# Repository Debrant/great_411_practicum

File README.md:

great_411_practicum
===================

Fall 2014 Industry Design Practicum at PSU

#[Project Wiki](https://github.com/Debrant/great_411_practicum/wiki)

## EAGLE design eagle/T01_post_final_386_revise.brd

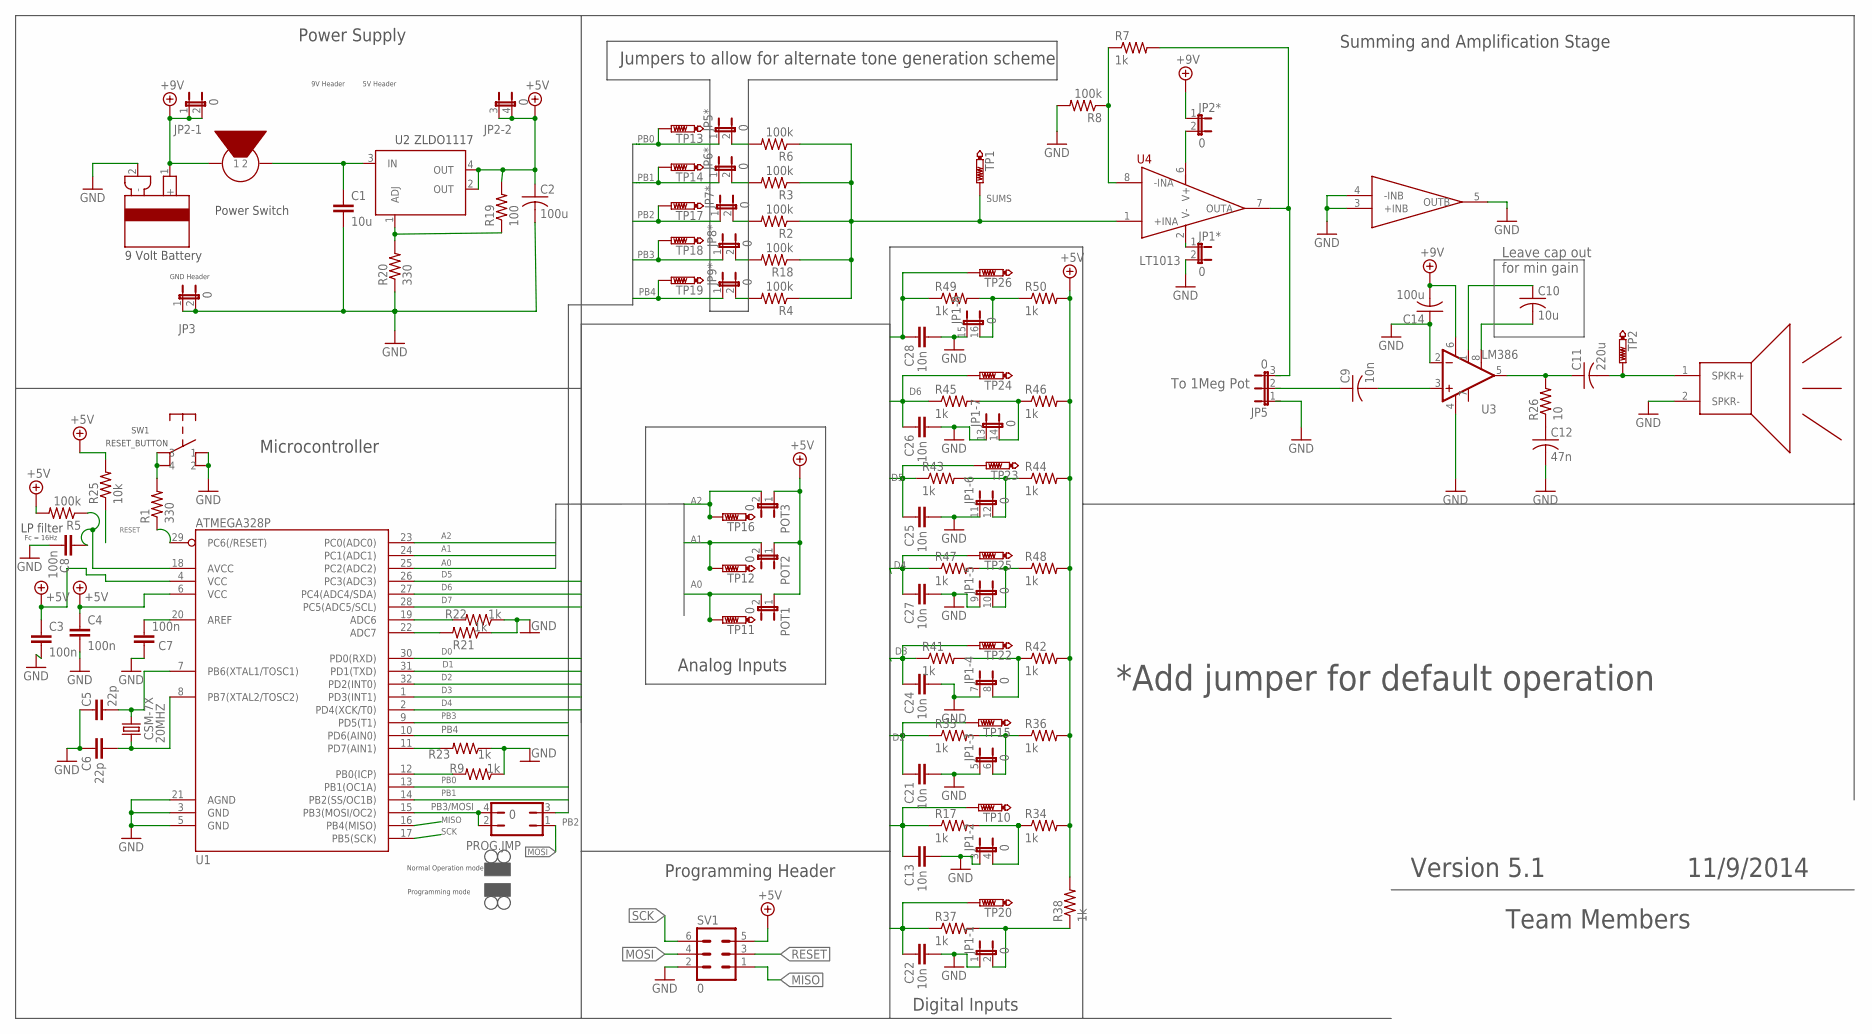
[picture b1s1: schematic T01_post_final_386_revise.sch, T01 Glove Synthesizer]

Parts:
20MHZ: CSM-7X; CSM-7X-DU
C1: 10u; 0603-CAP
C2: 100u; C075-042X103
C3, C4, C7, C8: 100n; 0603-CAP
C5, C6: 22p; 0603-CAP
C9: 10n; C025-030X050
C10: 10u; C025-030X050
C11: 220u; C025-030X050
C12: 47n; C025-030X050
C13, C21, C22, C24, C25, C26, C27, C28: 10n; 0603-CAP
C14: 100u; C025-030X050
JP1: 0; JP8Q
JP1*, JP2*, JP3, JP5*, JP6*, JP7*, JP8*, JP9*: 0; JP1
JP2: 0; JP2Q
JP5: 0; JP2
POT1, POT2, POT3: 0; JP1
PROG.JMP: 0; JP2Q
R1, R20: 330; 0603-RES
R2, R3, R4, R5, R6, R8, R18: 100k; 0603-RES
R7, R9, R17, R21, R22, R23, R34, R35, R36, R37, R38, R41, R42, R43, R44, R45, R46, R47, R48, R49, R50: 1k; 0603-RES
R19: 100; 0603-RES
R25: 10k; 0603-RES
R26: 10; 0204V
SV1: 0; MA03-2
SW1: RESET_BUTTON
TP1, TP2, TP10, TP11, TP12, TP13, TP14, TP15, TP16, TP17, TP18, TP19, TP20, TP22, TP23, TP24, TP25, TP26: PTR1B2,54; B2,54
U1: ATMEGA328P; TQFP32-08
U2: ZLDO1117; SOT223
U3: LM386; DIP08
U4: LT1013; SO08
U$1: SPEAKER; JP1
U$7: POWER_SWITCH; JP1
U$8: 9VOLTBATTERY; JP1

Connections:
+5V: C2.1, C3.1, C4.1, JP2.3 (1), JP2.4 (2), POT1.1, POT2.1, POT3.1, R5.2, R19.2, R25.2, R34.2, R36.2, R38.2, R42.2, R44.2, R46.2, R48.2, R50.2, SV1.5, U1.4 (VCC), U1.6 (VCC), U2.2 (OUT), U2.4 (OUT)
+9V: C14.2, JP2.1, JP2.2, JP2*.1, U3.6 (V+), U$7.1, U$8.1 (+)
A0: POT1.2, TP11.TP, U1.25 (PC2(ADC2))
A1: POT2.2, TP12.TP, U1.24 (PC1(ADC1))
A2: POT3.2, TP16.TP, U1.23 (PC0(ADC0))
D0: C22.2, R37.1, TP20.TP, U1.30 (PD0(RXD))
D1: C13.2, R17.1, TP10.TP, U1.31 (PD1(TXD))
D2: C21.2, R35.1, TP15.TP, U1.32 (PD2(INT0))
D3: C24.2, R41.1, TP22.TP, U1.1 (PD3(INT1))
D4: C27.2, R47.1, TP25.TP, U1.2 (PD4(XCK/T0))
D5: C25.2, R43.1, TP23.TP, U1.26 (PC3(ADC3))
D6: C26.2, R45.1, TP24.TP, U1.27 (PC4(ADC4/SDA))
D7: C28.2, R49.1, TP26.TP, U1.28 (PC5(ADC5/SCL))
GND: C1.2, C2.2, C3.2, C4.2, C5.2, C6.2, C7.2, C8.2, C12.2, C13.1, C14.1, C21.1, C22.1, C24.1, C25.1, C26.1, C27.1, C28.1, JP1.1, JP1.3 (1), JP1.5 (1), JP1.7 (1), JP1.9 (1), JP1.11 (1), JP1.13 (1), JP1.15 (1), JP1*.2, JP3.1, JP3.2, R8.2, R9.1, R20.1, R21.1, R22.1, R23.1, SV1.2, SW1.1, SW1.2, U1.3 (GND), U1.5 (GND), U1.21 (AGND), U3.2 (-IN), U3.4 (V-), U4.3 (+INB), U4.4 (-INB), U4.5 (OUTB), U$1.2 (SPKR-), U$8.2 (-)
MISO: SV1.1, U1.16 (PB4(MISO))
MOSI: PROG.JMP.1, SV1.4
unnamed: C7.1, U1.20 (AREF)
unnamed: JP1.8 (2), R41.2, R42.1
unnamed: JP1.12 (2), R43.2, R44.1
unnamed: R1.1, U1.29 (PC6(/RESET))
unnamed: R7.2, U4.7 (OUTA)
unnamed: 20MHZ.1, C5.1, U1.7 (PB6(XTAL1/TOSC1))
unnamed: 20MHZ.2, C6.1, U1.8 (PB7(XTAL2/TOSC2))
unnamed: C8.1, R5.1, U1.18 (AVCC)
unnamed: R21.2, U1.22 (ADC7)
unnamed: R22.2, U1.19 (ADC6)
unnamed: C9.2, U3.3 (+IN)
unnamed: JP1.6 (2), R35.2, R36.1
unnamed: R7.1, R8.1, U4.8 (-INA)
unnamed: R9.2, U1.12 (PB0(ICP))
unnamed: JP5*.2, R6.2
unnamed: JP9*.2, R4.2
unnamed: R1.2, SW1.3, SW1.4
unnamed: JP1.4 (2), R17.2, R34.1
unnamed: JP8*.2, R18.2
unnamed: C10.1, U3.1 (GAIN)
unnamed: C11.2, TP2.TP, U$1.1 (SPKR+)
unnamed: JP7*.2, R2.2
unnamed: JP2*.2, U4.6 (V+)
unnamed: R19.1, R20.2, U2.1 (ADJ)
unnamed: C1.1, U2.3 (IN), U$7.2
unnamed: JP6*.2, R3.2
unnamed: C10.2, U3.8 (GAIN)
unnamed: JP1.2, R37.2, R38.1
unnamed: C11.1, R26.2, U3.5 (OUT)
unnamed: C12.1, R26.1
unnamed: JP1.14 (2), R45.2, R46.1
unnamed: JP1.10 (2), R47.2, R48.1
unnamed: JP1.16 (2), R49.2, R50.1
PB0: JP5*.1, TP13.TP, U1.13 (PB1(OC1A))
PB1: JP6*.1, TP14.TP, U1.14 (PB2(SS/OC1B))
PB2: JP7*.1, PROG.JMP.3, TP17.TP
PB3: JP8*.1, TP18.TP, U1.9 (PD5(T1))
PB3/MOSI: PROG.JMP.2, PROG.JMP.4, U1.15 (PB3(MOSI/OC2))
PB4: JP9*.1, TP19.TP, U1.10 (PD6(AIN0))
PD7: R23.2, U1.11 (PD7(AIN1))
RESET: R25.1, SV1.3
SCK: SV1.6, U1.17 (PB5(SCK))
SUMS: R2.1, R3.1, R4.1, R6.1, R18.1, TP1.TP, U4.1 (+INA)
V-: JP1*.1, U4.2 (V-)

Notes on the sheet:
Power Switch
Programming Header
Digital Inputs
Power Supply
Microcontroller
Summing and Amplification Stage
Analog Inputs
LP filter
*Add jumper for default operation
5V Header
9V Header
GND Header
Fc = 16Hz
Jumpers to allow for alternate tone generation scheme
Programming mode
Normal Operation mode
Team Members
Version 5.1
11/9/2014
To 1Meg Pot
Leave cap out for min gain

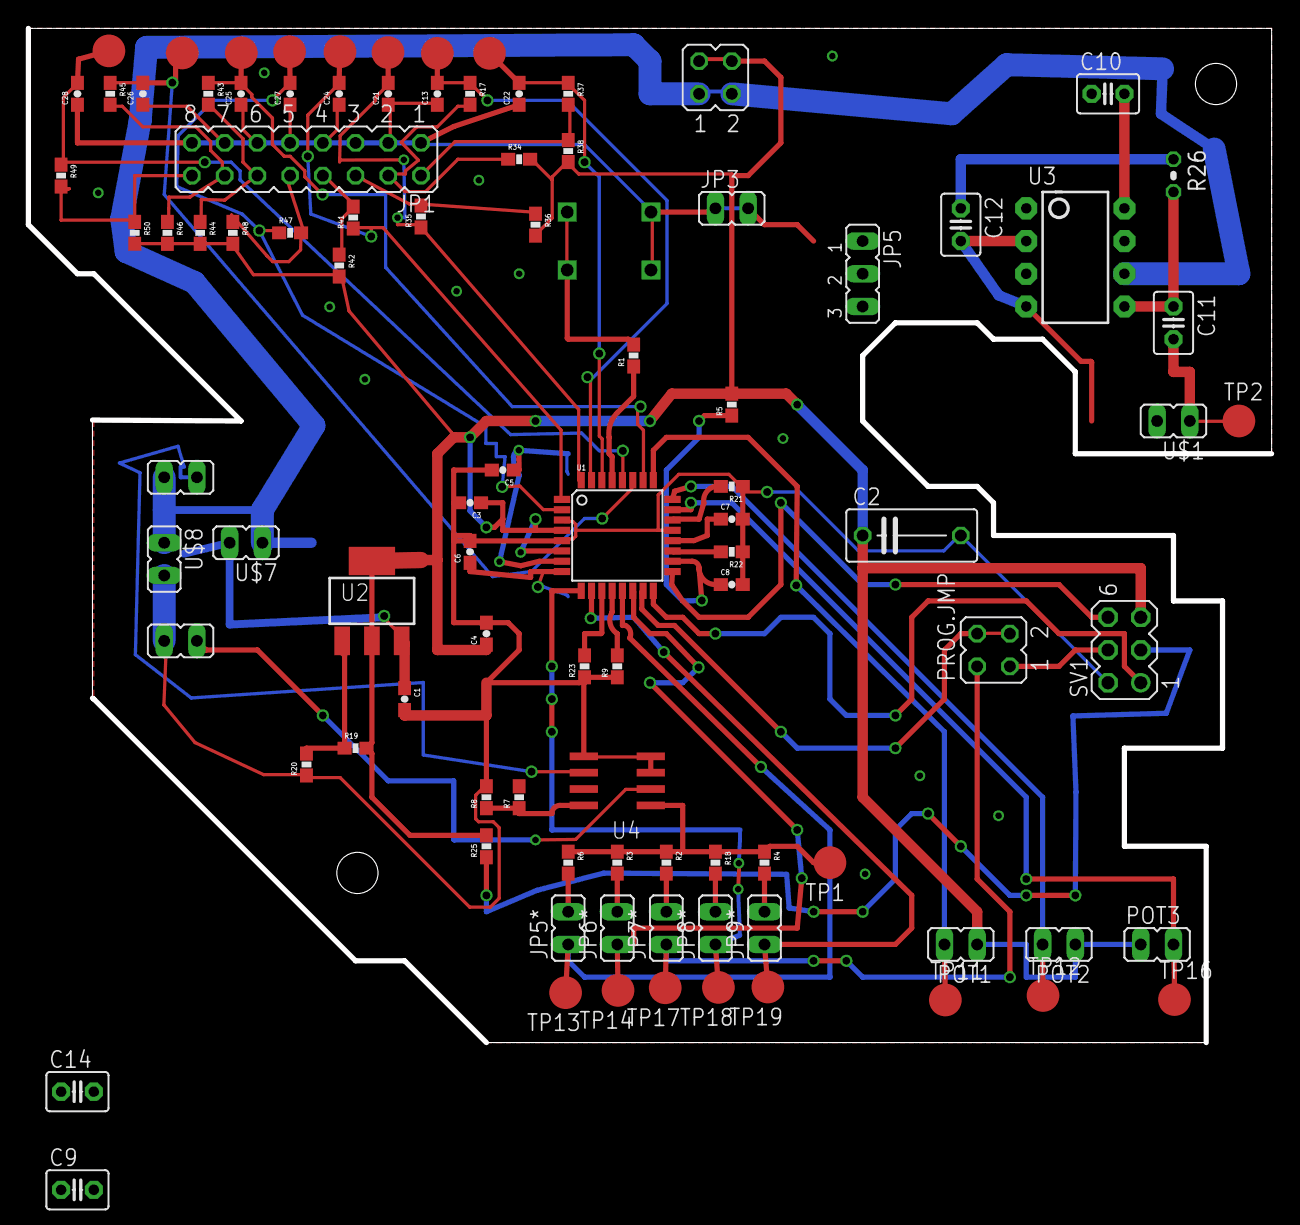
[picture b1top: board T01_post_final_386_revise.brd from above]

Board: 2 copper layers, 96.5 x 78.7 mm, 97 parts (1 on the bottom side), 60 nets.

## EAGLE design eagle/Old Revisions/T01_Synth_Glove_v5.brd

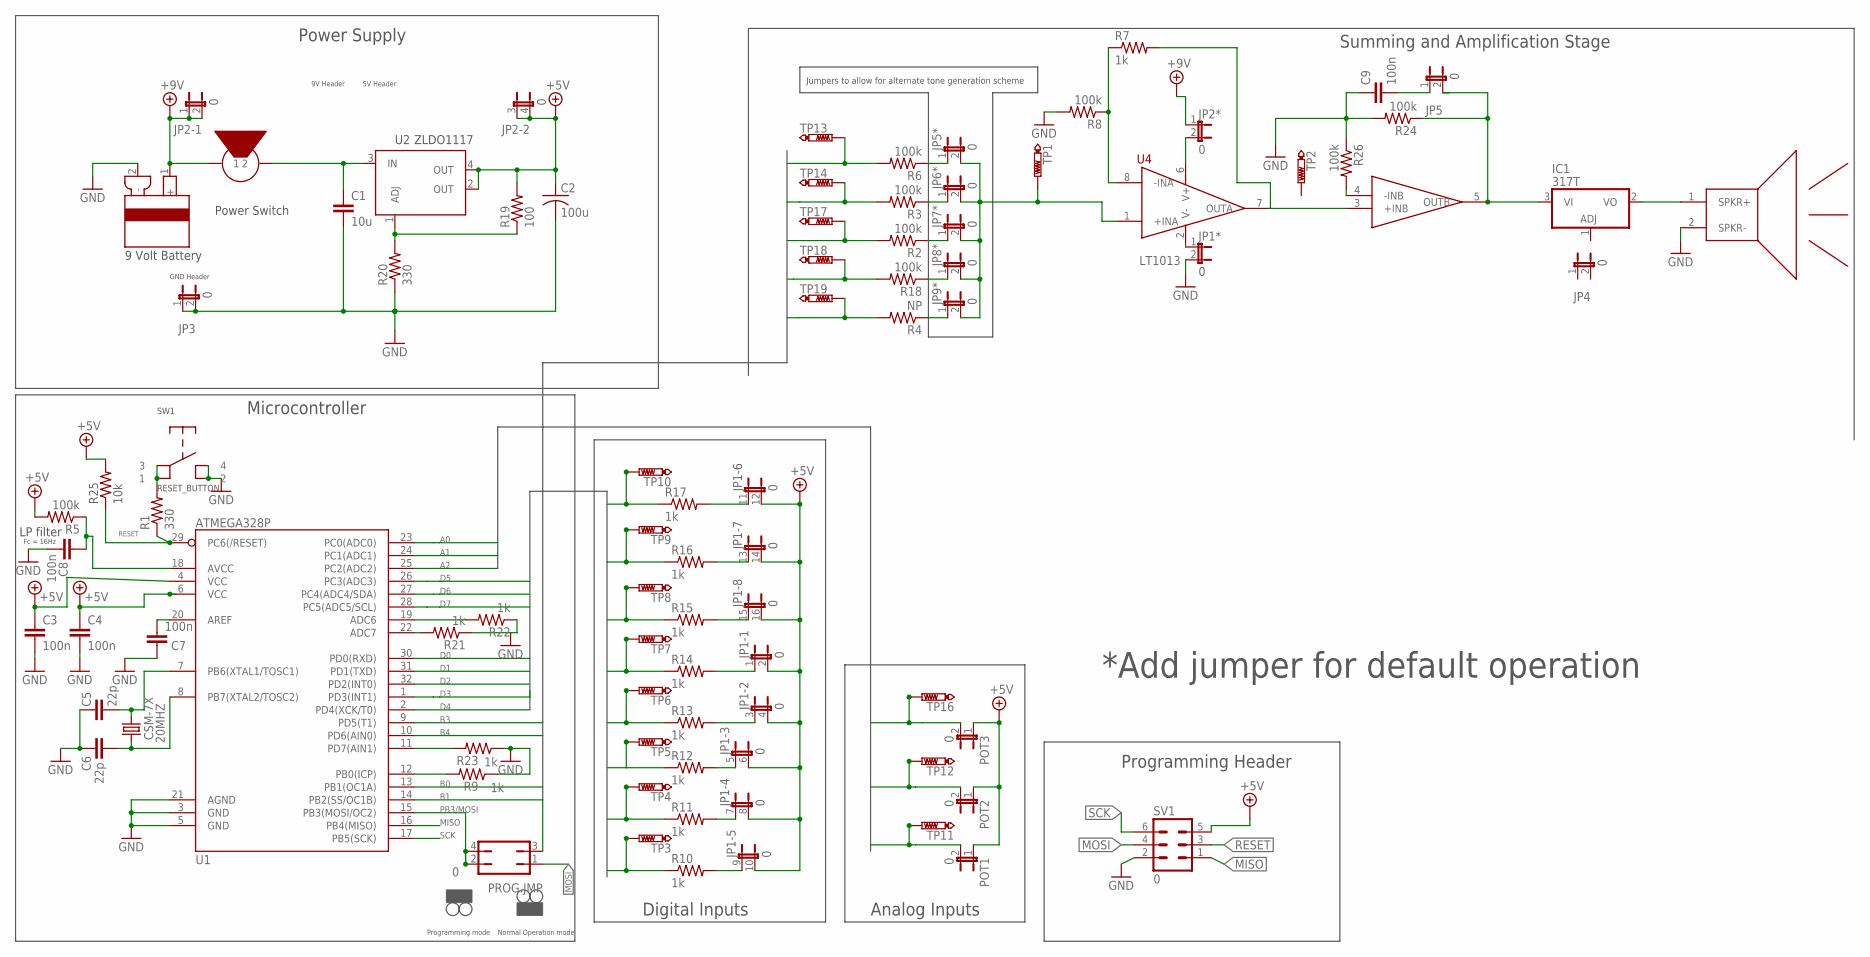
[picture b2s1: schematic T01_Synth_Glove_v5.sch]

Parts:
20MHZ: CSM-7X; CSM-7X-DU
C1: 10u; 0603-CAP
C2: 100u; C075-042X103
C3, C4, C7, C8, C9: 100n; 0603-CAP
C5, C6: 22p; 0603-CAP
IC1: 317T; TO220H
JP1: 0; JP8Q
JP1*, JP2*, JP3, JP4, JP5, JP5*, JP6*, JP7*, JP8*, JP9*: 0; JP1
JP2: 0; JP2Q
POT1, POT2, POT3: 0; JP1
PROG.JMP: 0; JP2Q
R1, R20: 330; 0603-RES
R2, R3, R5, R6, R8, R18, R24, R26: 100k; 0603-RES
R4: NP; 0603-RES
R7, R9, R10, R11, R12, R13, R14, R15, R16, R17, R21, R22, R23: 1k; 0603-RES
R19: 100; 0603-RES
R25: 10k; 0603-RES
SV1: 0; MA03-2
SW1: RESET_BUTTON
TP1, TP2, TP3, TP4, TP5, TP6, TP7, TP8, TP9, TP10, TP11, TP12, TP13, TP14, TP16, TP17, TP18, TP19: PTR1B2,54; B2,54
U1: ATMEGA328P; TQFP32-08
U2: ZLDO1117; SOT223
U4: LT1013; SO08
U$1: SPEAKER; JP1
U$7: POWER_SWITCH; JP1
U$8: 9VOLTBATTERY; JP1

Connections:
+5V: C2.1, C3.1, C4.1, JP1.2, JP1.4 (2), JP1.6 (2), JP1.8 (2), JP1.10 (2), JP1.12 (2), JP1.14 (2), JP1.16 (2), JP2.3 (1), JP2.4 (2), POT1.1, POT2.1, POT3.1, R5.2, R19.2, R25.2, SV1.5, U1.4 (VCC), U1.6 (VCC), U2.2 (OUT), U2.4 (OUT)
+9V: JP2.1, JP2.2, JP2*.1, U$7.1, U$8.1 (+)
A0: POT1.2, TP11.TP, U1.23 (PC0(ADC0))
A1: POT2.2, TP12.TP, U1.24 (PC1(ADC1))
A2: POT3.2, TP16.TP, U1.25 (PC2(ADC2))
B0: R6.2, TP13.TP, U1.13 (PB1(OC1A))
B1: R2.2, R3.2, TP14.TP, TP17.TP, U1.14 (PB2(SS/OC1B))
B2: PROG.JMP.3
B3: R18.2, TP18.TP, U1.9 (PD5(T1))
B4: R4.2, TP19.TP, U1.10 (PD6(AIN0))
D0: R10.1, TP3.TP, U1.30 (PD0(RXD))
D1: R11.1, TP4.TP, U1.31 (PD1(TXD))
D2: R12.1, TP5.TP, U1.32 (PD2(INT0))
D3: R13.1, TP6.TP, U1.1 (PD3(INT1))
D4: R14.1, TP7.TP, U1.2 (PD4(XCK/T0))
D5: R15.1, TP8.TP, U1.26 (PC3(ADC3))
D6: R16.1, TP9.TP, U1.27 (PC4(ADC4/SDA))
D7: R17.1, TP10.TP, U1.28 (PC5(ADC5/SCL))
GND: C1.2, C2.2, C3.2, C4.2, C5.2, C6.2, C7.2, C8.2, C9.1, JP1*.2, JP3.1, JP3.2, R8.2, R9.1, R20.1, R21.1, R22.1, R23.1, R24.2, R26.1, SV1.2, SW1.2, SW1.4, U1.3 (GND), U1.5 (GND), U1.21 (AGND), U$1.2 (SPKR-), U$8.2 (-)
MISO: SV1.1, U1.16 (PB4(MISO))
MOSI: PROG.JMP.1, SV1.4
unnamed: C7.1, U1.20 (AREF)
unnamed: JP5*.2, JP6*.2, JP7*.2, JP8*.2, JP9*.2, TP1.TP, U4.1 (+INA)
unnamed: JP1.9 (1), R10.2
unnamed: JP1.7 (1), R11.2
unnamed: JP1.5 (1), R12.2
unnamed: 20MHZ.1, C5.1, U1.7 (PB6(XTAL1/TOSC1))
unnamed: 20MHZ.2, C6.1, U1.8 (PB7(XTAL2/TOSC2))
unnamed: C8.1, R5.1, U1.18 (AVCC)
unnamed: R21.2, U1.22 (ADC7)
unnamed: R22.2, U1.19 (ADC6)
unnamed: JP1.3 (1), R13.2
unnamed: JP1.1, R14.2
unnamed: JP1.15 (1), R15.2
unnamed: JP1.13 (1), R16.2
unnamed: R7.1, R8.1, U4.8 (-INA)
unnamed: R9.2, U1.12 (PB0(ICP))
unnamed: JP5*.1, R6.1
unnamed: JP6*.1, R3.1
unnamed: R1.2, SW1.1, SW1.3
unnamed: JP1.11 (1), R17.2
unnamed: JP7*.1, R2.1
unnamed: R26.2, U4.4 (-INB)
unnamed: JP8*.1, R18.1
unnamed: IC1.2 (VO), U$1.1 (SPKR+)
unnamed: JP9*.1, R4.1
unnamed: JP2*.2, U4.6 (V+)
unnamed: R7.2, U4.7 (OUTA)
unnamed: R19.1, R20.2, U2.1 (ADJ)
unnamed: C1.1, U2.3 (IN), U$7.2
unnamed: C9.2, JP5.1
unnamed: IC1.3 (VI), JP5.2, R24.1, U4.5 (OUTB)
PB3/MOSI: PROG.JMP.2, PROG.JMP.4, U1.15 (PB3(MOSI/OC2))
PD7: R23.2, U1.11 (PD7(AIN1))
RESET: R1.1, R25.1, SV1.3, U1.29 (PC6(/RESET))
SCK: SV1.6, U1.17 (PB5(SCK))
V-: JP1*.1, U4.2 (V-)

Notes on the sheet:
Power Switch
Programming Header
Digital Inputs
Power Supply
Microcontroller
Summing and Amplification Stage
Analog Inputs
LP filter
*Add jumper for default operation
5V Header
9V Header
GND Header
Fc = 16Hz
Jumpers to allow for alternate tone generation scheme
Programming mode
Normal Operation mode

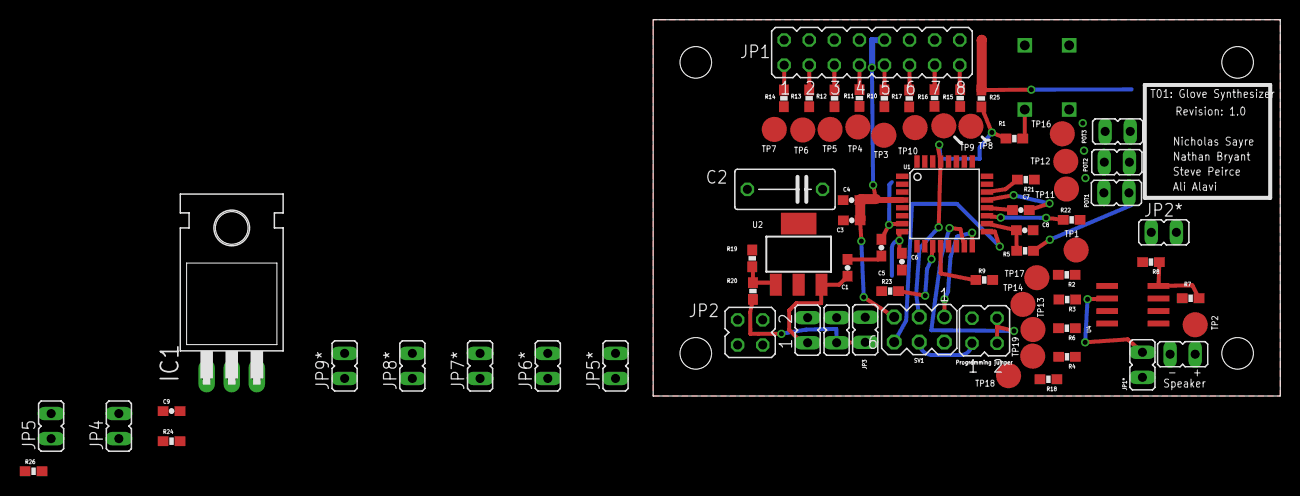
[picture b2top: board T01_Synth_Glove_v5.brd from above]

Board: 2 copper layers, 63.5 x 38.1 mm, 79 parts (1 on the bottom side), 56 nets.

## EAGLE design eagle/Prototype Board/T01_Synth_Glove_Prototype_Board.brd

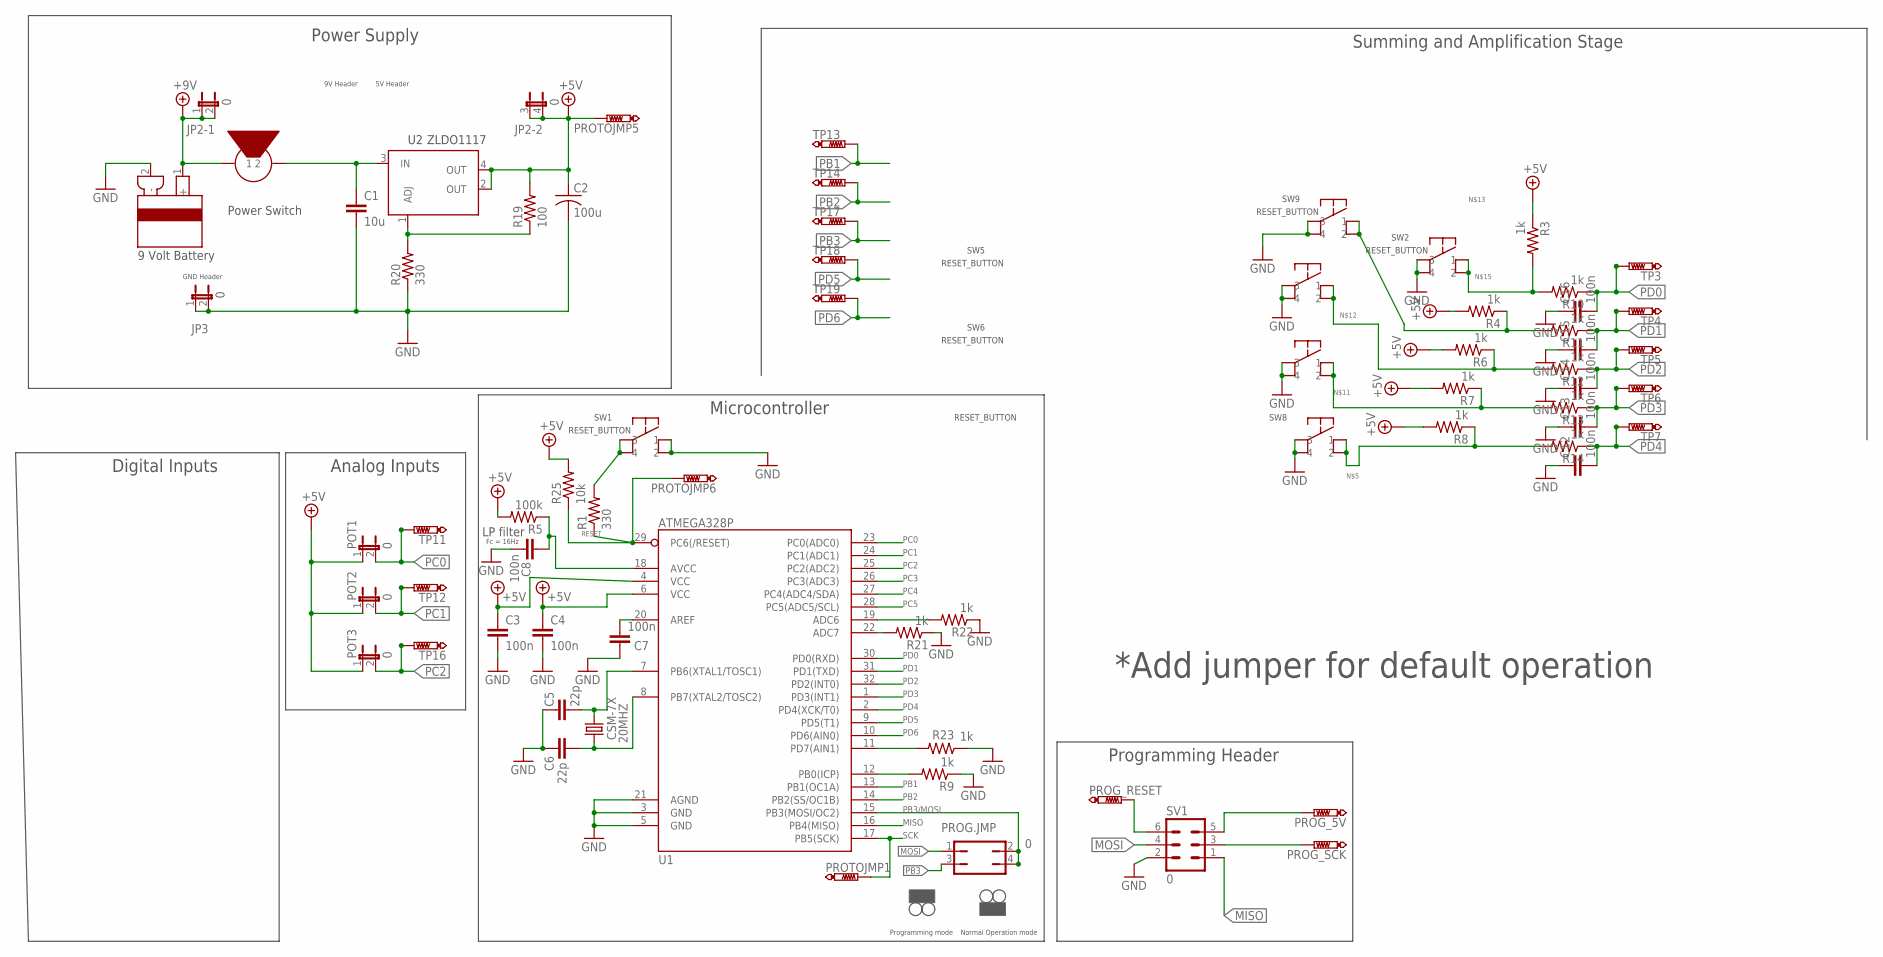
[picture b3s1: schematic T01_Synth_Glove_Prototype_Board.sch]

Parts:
20MHZ: CSM-7X; CSM-7X-DU
C1: 10u; 0603-CAP
C2: 100u; C075-042X103
C3, C4, C7, C8, C12, C13, C14, C15, C16: 100n; 0603-CAP
C5, C6: 22p; 0603-CAP
JP2: 0; JP2Q
JP3: 0; JP1
POT1, POT2, POT3: 0; JP1
PROG.JMP: 0; JP2Q
PROG_5V: PTR1B2,54; B2,54
PROG_RESET: PTR1B2,54; B2,54
PROG_SCK: PTR1B2,54; B2,54
PROTOJMP1, PROTOJMP5, PROTOJMP6: PTR1B2,54; B2,54
R1, R20: 330; 0603-RES
R3, R4, R6, R7, R8, R9, R10, R11, R12, R13, R14, R21, R22, R23: 1k; 0603-RES
R5: 100k; 0603-RES
R19: 100; 0603-RES
R25: 10k; 0603-RES
SV1: 0; MA03-2
SW1, SW2, SW5, SW6, SW8, SW9: RESET_BUTTON
TP3, TP4, TP5, TP6, TP7, TP11, TP12, TP13, TP14, TP16, TP17, TP18, TP19: PTR1B2,54; B2,54
U1: ATMEGA328P; TQFP32-08
U2: ZLDO1117; SOT223
U$7: POWER_SWITCH; JP1
U$8: 9VOLTBATTERY; JP1

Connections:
+5V: C2.1, C3.1, C4.1, JP2.3 (1), JP2.4 (2), POT1.1, POT2.1, POT3.1, PROTOJMP5.TP, R3.1, R4.2, R5.2, R6.2, R7.2, R8.2, R19.2, R25.2, U1.4 (VCC), U1.6 (VCC), U2.2 (OUT), U2.4 (OUT)
+9V: JP2.1, JP2.2, U$7.1, U$8.1 (+)
GND: C1.2, C2.2, C3.2, C4.2, C5.2, C6.2, C7.2, C8.2, C12.1, C13.1, C14.1, C15.1, C16.1, JP3.1, JP3.2, R9.1, R20.1, R21.1, R22.1, R23.1, SV1.2, SW1.1, SW1.2, SW2.3, SW2.4, SW5.3, SW5.4, SW6.3, SW6.4, SW8.3, SW8.4, SW9.3, SW9.4, U1.3 (GND), U1.5 (GND), U1.21 (AGND), U$8.2 (-)
JP3: PROG_SCK.TP, SV1.3
MISO: SV1.1, U1.16 (PB4(MISO))
MOSI: PROG.JMP.1, SV1.4
unnamed: C7.1, U1.20 (AREF)
unnamed: PROG_5V.TP, SV1.5
unnamed: R8.1, R14.2, SW8.1, SW8.2
unnamed: 20MHZ.1, C5.1, U1.7 (PB6(XTAL1/TOSC1))
unnamed: 20MHZ.2, C6.1, U1.8 (PB7(XTAL2/TOSC2))
unnamed: C8.1, R5.1, U1.18 (AVCC)
unnamed: R21.2, U1.22 (ADC7)
unnamed: R22.2, U1.19 (ADC6)
unnamed: R7.1, R13.2, SW6.1, SW6.2
unnamed: R6.1, R12.2, SW5.1, SW5.2
unnamed: R4.1, R11.2, SW9.1, SW9.2
unnamed: R3.2, R10.2, SW2.1, SW2.2
unnamed: R9.2, U1.12 (PB0(ICP))
unnamed: R1.2, SW1.3, SW1.4
unnamed: R19.1, R20.2, U2.1 (ADJ)
unnamed: C1.1, U2.3 (IN), U$7.2
PB1: TP13.TP, U1.13 (PB1(OC1A))
PB2: TP14.TP, U1.14 (PB2(SS/OC1B))
PB3: PROG.JMP.3, TP17.TP
PB3/MOSI: PROG.JMP.2, PROG.JMP.4, U1.15 (PB3(MOSI/OC2))
PC0: POT1.2, TP11.TP, U1.23 (PC0(ADC0))
PC1: POT2.2, TP12.TP, U1.24 (PC1(ADC1))
PC2: POT3.2, TP16.TP, U1.25 (PC2(ADC2))
PC3: U1.26 (PC3(ADC3))
PC4: U1.27 (PC4(ADC4/SDA))
PC5: U1.28 (PC5(ADC5/SCL))
PD0: C16.2, R10.1, TP3.TP, U1.30 (PD0(RXD))
PD1: C15.2, R11.1, TP4.TP, U1.31 (PD1(TXD))
PD2: C14.2, R12.1, TP5.TP, U1.32 (PD2(INT0))
PD3: C13.2, R13.1, TP6.TP, U1.1 (PD3(INT1))
PD4: C12.2, R14.1, TP7.TP, U1.2 (PD4(XCK/T0))
PD5: TP18.TP, U1.9 (PD5(T1))
PD6: TP19.TP, U1.10 (PD6(AIN0))
PD7: R23.2, U1.11 (PD7(AIN1))
PJ4: PROG_RESET.TP, SV1.6
RESET: PROTOJMP6.TP, R1.1, R25.1, U1.29 (PC6(/RESET))
SCK: PROTOJMP1.TP, U1.17 (PB5(SCK))

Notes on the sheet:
Power Switch
Programming Header
Digital Inputs
Power Supply
Microcontroller
Summing and Amplification Stage
Analog Inputs
LP filter
*Add jumper for default operation
5V Header
9V Header
GND Header
Fc = 16Hz
Programming mode
Normal Operation mode

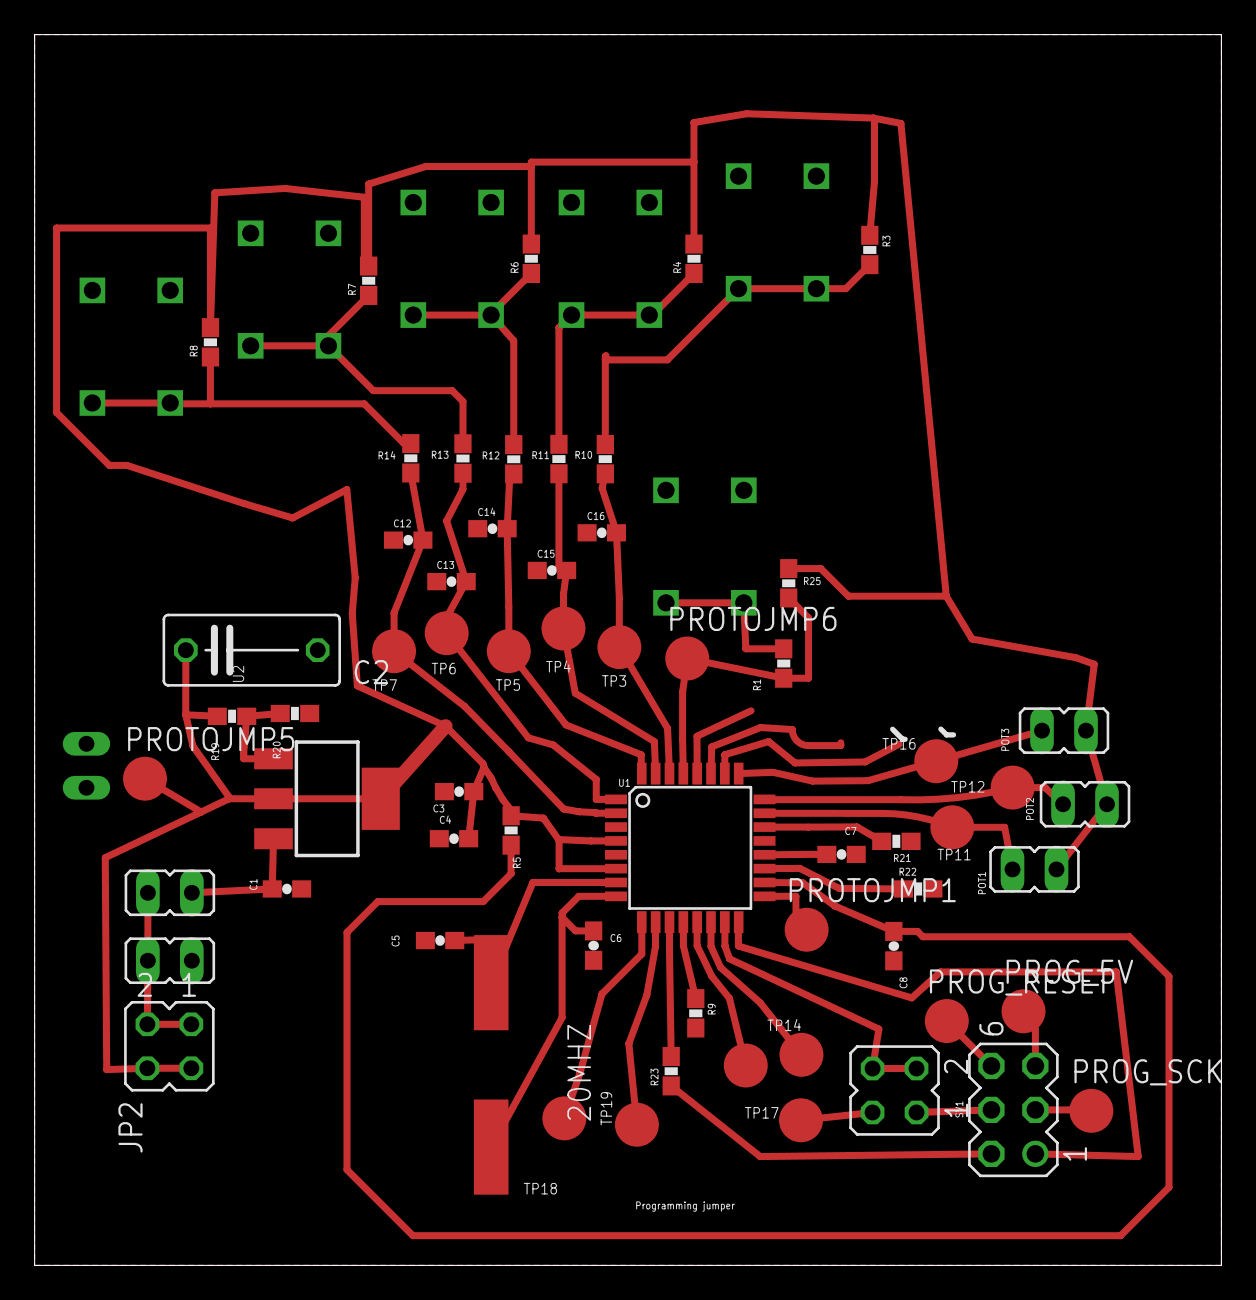
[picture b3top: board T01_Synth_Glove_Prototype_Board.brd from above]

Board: 2 copper layers, 68.6 x 71.1 mm, 69 parts (1 on the bottom side), 40 nets.

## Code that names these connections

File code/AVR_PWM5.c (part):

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
	/*PRTIMx BIT MUST BE WRITTEN 0 TO ENABLE TIMER/COUNTERS P.94 DS*/
	/*OUTPUT COMPARE REGISTERS, OUR (5) PWM OUTPUTS:*/
	OCR0A = TONE0.PULSE_WIDTH;//PIN 10, PD6
	OCR0B = TONE1.PULSE_WIDTH;//PIN 9,  PD5
	OCR1AL = TONE2.PULSE_WIDTH;//PIN 13, PB1
	OCR1BL = TONE3.PULSE_WIDTH;//PIN 14, PB2
	OCR2A = TONE4.PULSE_WIDTH;//PIN 15, PB3

	/*TIMER INTERRUPT FLAG REGISTERS:*/
	/*P.110***********COMPARE0B**COMPARE0A*TIMER OVERFLOW*******************/
	/*BITS:[7:3]RES, [2]OCF0B, [1]OCF0A, [0]TOV0*/
	/*MAY NEED AN ISR THAT IS A CATCH-ALL, DIRECTS BASED ON FLAGS...*/
	/*SET WHEN OVERFLOW OCCURS, CLEARED BY INTERRUPT TIFRnx:*/
	//TIFR0 |= ();//8-BIT->PORTS:  [OC0A,PD6], [OC0B,PD5]
	//TIFR1 |= ();//16-BIT->PORTS: [OC1A,PB1], [OC1B,PB2]
	//TIFR2 |= ();//8-BIT->PORTS:  [OC2A,PB3], [OC2B,PD3]

	//TIMSK0 |= ((1<<OCIE0A) | (1<<OCIE0B));
	//TIMSK1 |= ((1<<OCIE1A) | (1<<OCIE1B));
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}/*end init*/

void adc_init(){
	//ADMUX |= ((1<<MUX0) | (1<<REFS0)); //ADC1 ON PIN PC1, PIN 24, (TQFP AND DIP)
	ADMUX = 0b01100011; //ADC1 ON PIN PC1, PIN 24, (TQFP AND DIP), P.254
	ADCSRA |= ((1<<ADEN) | (1<<ADIE) | (1<<ADATE | (1<<ADPS0)));//P255,256
	//ADCSRB |= ((1<<ADTS2) | (1<<ADTS1));
	ADCSRB = 0x00; //FREE RUNNING MODE
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
void pwm_update(uint8_t ADC_IN){
		/*TODO: TRY SETTING ONE OCRx SETTING TO '0', SPOOF MULTI IO*/
	if(!INPUT.SW3){//PD0
		OCR1AL = TONE0.PULSE_WIDTH;
		//OCR1AL = (ADC_IN/TONE0.PULSE_WIDTH);
		//OCR1AL = TONE0.PULSE_WIDTH;
		OCR1BL = (ADC_IN/(TONE0.PULSE_WIDTH/16));
	}		
	if(!INPUT.SW4){//PD1
		OCR1AL = TONE1.PULSE_WIDTH*4;
		OCR1BL = TONE3.PULSE_WIDTH*32;
	}
	if(!INPUT.SW5){//PD2
		OCR1AL = TONE2.PULSE_WIDTH*32;
		OCR1BL = TONE2.PULSE_WIDTH*32;
	}
	if(!INPUT.SW6){//PD3
		OCR1AL = TONE3.PULSE_WIDTH*32;
		OCR1BL = TONE1.PULSE_WIDTH*32;
	}
	if(!INPUT.SW7){//PD4
		OCR1AL = TONE4.PULSE_WIDTH*32;
		OCR1BL = TONE4.PULSE_WIDTH*4;
	}
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	PORTB = 0x0; /*INITIALIZE ALL TO "OFF" STATE*/
	
	//PC[5:3] ARE INPUTS SO MAKE SURE 0'S ARE WRITTEN:
	//DDRC = 0b00000000;//TODO MAKE SURE PC6 NOT LOW, RESET!
	DDRC &= 0b10000000;//TODO MAKE SURE PC6 NOT LOW, RESET!
	PORTC = 0b01111000;//TURN ON PULLUPS

	//PD0[4:1] ARE INPUTS, PD[6:5] ARE OUTPUTS:
	//7  6  5  4  3  2  1  0
	//0  1  1  0  0  0  0  0
	DDRD = 0b01100000;
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
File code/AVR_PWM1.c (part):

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	/*MAY NEED AN ISR THAT IS A CATCH-ALL, DIRECTS BASED ON FLAGS...*/
	/*SET WHEN OVERFLOW OCCURS, CLEARED BY INTERRUPT TIFRnx:*/
	//TOVn, BIT[0]
	//TIFR0 |= ();//8-BIT->PORTS:  [OC0A,PD6], [OC0B,PD5]
	//TIFR1 |= ();//16-BIT->PORTS: [OC1A,PB1], [OC1B,PB2]
	//TIFR2 |= ();//8-BIT->PORTS:  [OC2A,PB3], [OC2B,PD3]
	
	/*TIMER COUNTER CLOCK SOURCES:*/
	//CURRENTLY NON-PWM, OVERFLOW AT TOP (OCRx), CTC MODE->TOGGLE OUTPUT
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	/*PORT DEFS on PAGE 92 of ATMEL DATASHEET*/	
	//7  6  5  4  3  2  1  0
	//0  0  0  1  0  0  0  0
	DDRB  &= ~(1<<PB4);  /*PORT B IS NOW ALL OUTPUTS, EXCEPT PB4!*/
	PORTB = 0b00010000; /*INITIALIZE ALL TO "OFF" STATE, PB4 PULLUP ON*/
	
	//PD3, 5, 6 ARE INPUTS, REST OUTPUTS:
	//7  6  5  4  3  2  1  0
	//0  1  1  0  1  0  0  0
	DDRD = 0b01101000;
	//DDRD  |=  ((1<<PB7) | (1<<PB5) | (1<<PB3));  /*PORTD3,5,6 ARE OUTPUTS, OTHERS ARE INPUT INTERRUPTS*/ 
//	PORTD = 0b01101111;
	PORTD = 0b10010111; /*TURN ON PULLUPS ON INPUTS, OFF STATE FOR OUTPUTS*/

	EICRA |= (1<<ISC00); /*EXTERNAL INTERRUPT CONTROL REGISTER A*/	
	EIMSK |= (1<<INT0);  /* TURN ON INTERRUPT 0, PIN PD2*/
	PCICR |= (1<<PCIE2 | 1<<PCIE0);/*ENABLE PCINTS ON BANK 0,2*/
	
	PCMSK0 |= (1<<PCINT4); /*BANK 0, PCINT 4 IS PIN PB4*/
	PCMSK2 |= ((1<<PCINT16) | (1<<PCINT17) | (1<<PCINT20)); 
	TIMSK0 |= ((1<<OCIE0A) | (1<<OCIE0B));
	TIMSK2 |= ((1<<OCIE2A) | (1<<OCIE2B) | (1<<TOIE2)); 
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
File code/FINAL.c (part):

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	
	ADMUX &= 0xF0; 	     //MASK OFF LOWER BITS FOR CONFIGURATION
	ADMUX |= (1<<REFS0); //SET REFERENCE TO AVCC W/ CAP TO GROUND
	ADMUX |= (1<<MUX0);  //INITIALIZE TO ADC1, PC1, PIN 24
	ADCSRA |= (1<<ADEN); //P255,256
	_delay_ms(1); 	     //ADEN ENABLE TAKES ~12 ADC CLK CYCLES, @~200KHZ
	ADCSRA |= (1<<ADATE);//SET TO AUTO TRIGGER ADC CONVERSION EVENT
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	PORTB = 0x0; /*INITIALIZE ALL TO "OFF" STATE*/
	
	//PC[5:3] ARE INPUTS SO MAKE SURE 0'S ARE WRITTEN:
	//DDRC &= 0b10000000;//MAKE SURE PC6 NOT LOW, RESET!
	DDRC &= ~((1<<PC5)|(1<<PC4)|(1<<PC3));//MAKE SURE PC6 NOT LOW, RESET!
	PORTC |= ((1<<PC5) | (1<<PC4) | (1<<PC3));//TURN ON PULLUPS
	//PORTC = 0b01111000;//TURN ON PULLUPS

	//PD0[4:1] ARE INPUTS, PD[6:5] ARE OUTPUTS:
	DDRD  = 0b01100000;
	PORTD = 0b00011111; /*0x1E-TURN ON PULLUPS ON INPUTS, OFF STATE FOR OUTPUTS*/
	
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
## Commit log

2014-10-12 AHS matrix
2014-10-12 Atmega328 Datasheets
2014-10-12 Eagle Schematic template
2014-10-18 Testing revision control
2014-10-18 Programmer
    Added programmer to schematic
2014-10-23 Update 23
2014-10-24 Requirements document rough draft
2014-10-26 Burn script for AVRDUDE and AVRDRAGOn
2014-10-26 AVRDUDE burn script for AVRDRAGON
2014-10-26 Tutorial on AVR-GCC Toolchain
2014-10-26 AVRDUDE burn script on AVRDRAGON, updated BAUD
2014-10-26 AVR Docs
2014-10-26 LT1013_datasheet
2014-10-27 homework3
2014-10-27 Create gh-pages branch via GitHub
2014-10-27 Continued work on eagle schematic + project library
2014-10-27 Though_hw3X
2014-10-27 test
2014-10-27 PDSv2
2014-10-28 SWITCHED INPUT LED TEST CODE
2014-10-28 AVR Technical Reference Manual
2014-10-28 AVR Instruction Set - Syntax and Sample Code, etc.
2014-10-30 schematicv2
2014-10-31 AVR CODE IMPLEMENTING INTERRUPTS TO LIGHT LED, USE PIN 4 AS INPUT!
2014-10-31 organizing
2014-10-31 MULTIPLE INPUT, CORRESPONDING OUTPUT INTERRUPT BASED TEST PROG USE PINS: 14, 15, 16, 17, 18
2014-10-31 BACKING UP NEWEST CODE, PWM IMPLEMENTATION, BROKEN!!
2014-10-31 issues with using a summing amp
2014-11-01 added libraries
2014-11-02 team meet
2014-11-02 WORKING interrupt based code, multiple input outputs
2014-11-02 WORKING interrupt based multi IO code
2014-11-03 ERC free schematic
    ERC free complete schematic, added new devices to the eagle library,
    more documentation
2014-11-03 WORKING AVR MULTI IO CODE, 5 INPUT, 5 OUTPUT
2014-11-03 meeting 11/1
2014-11-05 DRC error free board, and DRU + CAM files
2014-11-05 Eagle file housekeeping
2014-11-06 2 working tones, switches need debouncing, currently VERY ugly, will clean up tomorrow...er later today...
2014-11-07 Schematic update, Started Prototype Board
2014-11-07 updatNo15
2014-11-07 Prototype Board Amplifier Stage
    For making prototype in EPL
2014-11-07 Prototype board update
2014-11-07 linking to repo for proto
2014-11-07 test board revisions
2014-11-07 clearing deleted files
2014-11-07 lost file return
2014-11-07 Gerber Files for Amp Board
2014-11-08 Update, more CAM files
2014-11-08 Revisions and more CAM
2014-11-08 WORKING backup, multiple buttons/tones, still NOT perfect, just a backup!
2014-11-08 Project Schedule
    Started project schedule and added all of the tasks (quite a bit more
    than I expected). Also started working on the timeline which needs to be
    completed as well as assigning resources.
2014-11-08 issue 5 and greenberg requsts
2014-11-09 Finished Project Management
    Finished the project management but could definitely use a second pair
    of eyes (especially with the resources).
2014-11-09 Board revision with debounce and 386
2014-11-10 2 eagle versions with mostly no errors
2014-11-10 Revised Schedule
    Revised based on what Nathan and I discussed.
2014-11-10 DRC FREE up to date board
2014-11-10 revision to board
2014-11-10 added mounting holes
2014-11-10 Alternate layout
2014-11-10 last minute
2014-11-10 Eagle housekeeping + final board revision
2014-11-10 Schedule
2014-11-10 revision to schedule--ie--what was turned in
2014-11-10 adding images
2014-11-12 Invoices
    Component and Board costs outlined
2014-11-12 Backup of current code, will be revised prior to completion
2014-11-12 ZLDO Vout
2014-11-16 Alternate Audio Amplifier IC datasheet
2014-11-16 images from 11/15
2014-11-17 UML doc
2014-11-17 wiki updates
2014-11-17 wiki page for UML
2014-11-19 Synth Glove Board info (Attention: Steve)
2014-11-22 amp fixes
2014-11-24 CURRENT CODE, BROKEN?
2014-11-24 homework 6
2014-11-24 Homework 6 update
2014-11-24 HW6 UD3
2014-11-26 Updated pin list, set up to test IO, put LEDs on OUTPUTS!
2014-11-26 Extension of AVR_INTS2_rev2.c, using new pins, should work to implement PWM out, but NO ADC input
2014-11-26 isp programming inst for atmega
2014-11-28 black friday
2014-11-30 final board and enclosure mods
2014-12-01 case planning
2014-12-02 case plans **please read notes in file
2014-12-05 current workingEST code, 2+ tones
2014-12-07 ADDING IN ADC INPUT, STILL BUGGY
2014-12-10 Best so far, multiple tones, ADC and variants
2014-12-10 Furthest code so far, ADC, Multiple tones, modifiers. added coments
2014-12-10 closing in on done #1
2014-12-10 closing in on done #2
2014-12-11 closing in on done #3
2014-12-11 FINAL revision, still in the works, but our template
2014-12-11 more of the same
2014-12-11 Presentation PPT draft
    First draft of PPT slides. Incomplete presentation.
2014-12-11 Revert "Presentation PPT draft"
    This reverts commit ba2bd48bf08137bbf3038c8e6099d65f82325c4a.
2014-12-11 PPT Slides Draft 1
    First draft of PPT presentation.
2014-12-11 Still being stoopid
2014-12-11 'helllll'
2014-12-11 PPT draft1
    Incomplete presentation. First draft.
2014-12-11 PPT presentation first draft
    First draft of slides
2014-12-11 PPT presentation first draft
    Incomplete presentation. First set of Slides.
2014-12-11 PPT presentation - almost done
    Second draft of PPT slides. Almost done.
2014-12-11 PPT second draft
    Second draft of slides. Almost done.
2014-12-11 Completed PPT slides
    Final PPT slides
2014-12-11 Presentation slides
    Final presentation slides
2014-12-11 Prototype photos
    Photos of the completed prototype
2014-12-11 Seriously folks??
2014-12-11 Real final presentation
    Minor adjustments for lessons learned.
2014-12-11 PPT PDF
    PDF of actual presentation
2014-12-11 Final code

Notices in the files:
parts and their libraries:
SparkFun-Capacitors: Licensing: Creative Commons ShareAlike 4.0 International - https://creativecommons.org/licenses/by-sa/4.0
